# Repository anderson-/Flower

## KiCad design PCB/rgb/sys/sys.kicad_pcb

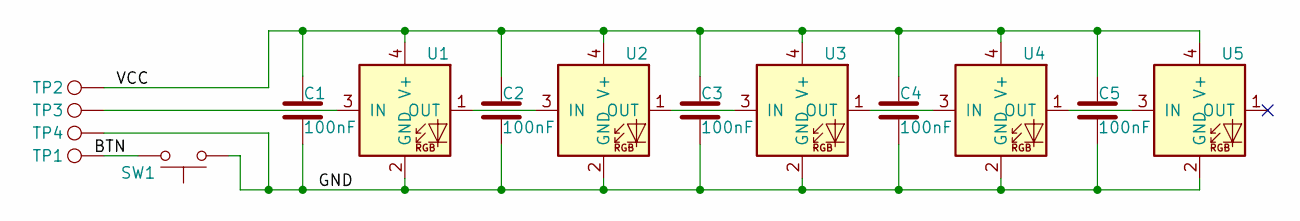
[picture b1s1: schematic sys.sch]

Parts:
C1, C2, C3, C4, C5: 100nF; C_0603_1608Metric
SW1: PushButtonSquare; SW_SPST_TL3342
TP1, TP2, TP3, TP4: TestPoint; TestPoint_Pad_D1.0mm
U1, U2, U3, U4, U5: WS2812B-2020; WS2812-2020

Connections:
/BTN: SW1.2, TP1.1
/GND: C1.2, C2.2, C3.2, C4.2, C5.2, SW1.1, TP4.1, U1.2 (GND), U2.2 (GND), U3.2 (GND), U4.2 (GND), U5.2 (GND)
/VCC: C1.1, C2.1, C3.1, C4.1, C5.1, TP2.1, U1.4 (V+), U2.4 (V+), U3.4 (V+), U4.4 (V+), U5.4 (V+)
unnamed: TP3.1, U1.3 (IN)
unnamed: U1.1 (OUT), U2.3 (IN)
unnamed: U2.1 (OUT), U3.3 (IN)
unnamed: U3.1 (OUT), U4.3 (IN)
unnamed: U4.1 (OUT), U5.3 (IN)

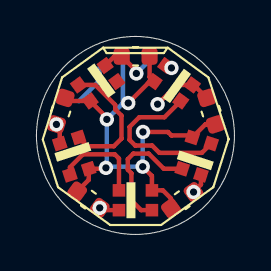
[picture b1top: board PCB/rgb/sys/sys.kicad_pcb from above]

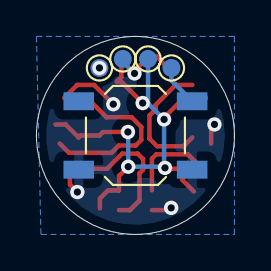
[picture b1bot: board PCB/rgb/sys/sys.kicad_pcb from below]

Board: 2 copper layers, 11.0 x 11.0 mm, 15 parts (5 on the bottom side), 8 nets.

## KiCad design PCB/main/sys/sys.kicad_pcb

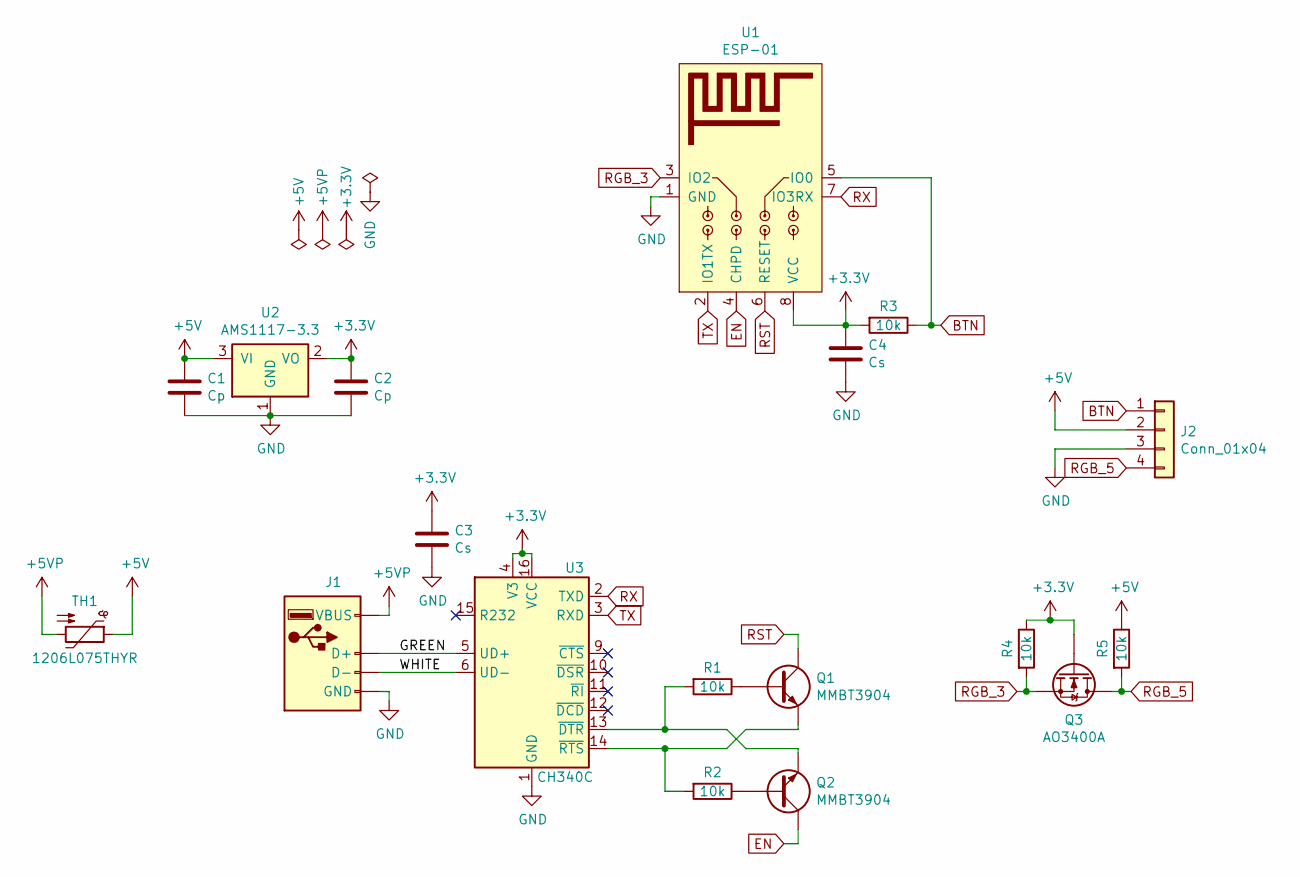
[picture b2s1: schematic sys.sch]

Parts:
C1, C2: Cp; C_1206_3216Metric
C3, C4: Cs; C_0805_2012Metric
J1: USB_PCB; USB_PCB_Edge
J2: Conn_01x04; PinHeader_1x04_P2.00mm_Vertical
Q1, Q2: MMBT3904; SOT-23
Q3: AO3400A; SOT-23
R1, R2, R3, R4, R5: 10k; R_0805_2012Metric
TH1: 1206L075THYR; R_1206_3216Metric
U1: ESP-01; ESP_01
U2: AMS1117-3.3; SOT-223-3_TabPin2
U3: CH340C; SOIC-16_3.9x9.9mm_P1.27mm

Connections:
+3V3: C2.1, C3.1, C4.1, Q3.1 (G), R3.2, R4.1, U1.8 (VCC), U2.2 (VO), U3.4 (V3), U3.16 (VCC)
+5V: C1.1, J2.2, R5.1, TH1.1, U2.3 (VI)
+5VP: J1.VIN (VBUS), TH1.2
/GREEN: J1.D+, U3.5 (UD+)
/WHITE: J1.D-, U3.6 (UD-)
BTN: J2.1, R3.1, U1.5 (IO0)
EN: Q2.3 (C), U1.4 (CHPD)
GND: C1.2, C2.2, C3.2, C4.2, J1.GND, J2.3, U1.1 (GND), U2.1 (GND), U3.1 (GND)
unnamed: Q1.1 (B), R1.1
unnamed: Q1.2 (E), R2.2, U3.14 (~RTS)
unnamed: Q2.1 (B), R2.1
unnamed: Q2.2 (E), R1.2, U3.13 (~DTR)
RGB_3: Q3.2 (S), R4.2, U1.3 (IO2)
RGB_5: J2.4, Q3.3 (D), R5.2
RST: Q1.3 (C), U1.6 (RESET)
RX: U1.7 (IO3RX), U3.2 (TXD)
TX: U1.2 (IO1TX), U3.3 (RXD)

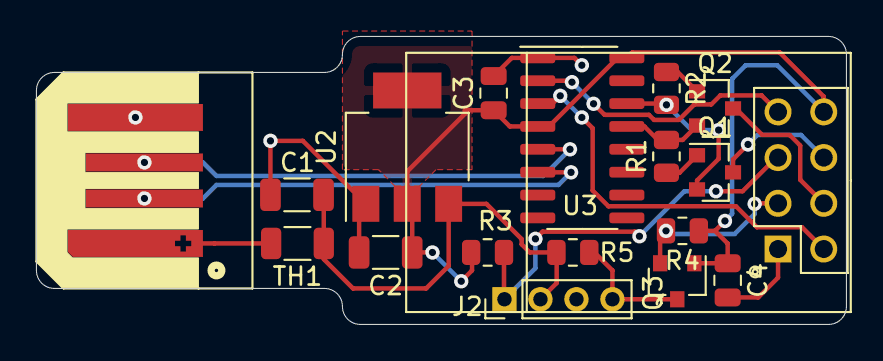
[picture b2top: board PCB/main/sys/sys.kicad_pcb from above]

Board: 2 copper layers, 45.0 x 16.0 mm, 18 parts (0 on the bottom side), 17 nets.

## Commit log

2021-07-19 Add main board
2021-07-19 Add indicator board
